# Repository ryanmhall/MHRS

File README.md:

# PPG-DaLiA heart-rate processing (single subject)

This README covers `ppg_analysis.py`. The script reads one subject from the PPG-DaLiA dataset and estimates heart rate from the wrist PPG. It then compares that estimate with the chest-ECG ground truth before and after a simple cleaning step.

**Requirements:** Python 3, `numpy`, `scipy`, `pandas`, `matplotlib`

**Run:** `ppg_analysis.py`. The file path is set at the top of the script.

## Pipeline at a glance

```
S1.pkl
 ├─ data['label'] ─────────────────────────────────────────► ground-truth HR (chest ECG)
 └─ data['signal']['wrist']['BVP']  (raw PPG, 64 Hz)
       │
       ├─ 1. band-pass 0.5–4 Hz (zero-phase Butterworth)
       ├─ 2. cut into 8 s windows, stepped every 2 s (same grid as the labels)
       ├─ 3. per window: Hann taper → zero-padded FFT → strongest peak in 40–200 BPM
       │                                                   ───► "Before" HR
       └─ 4. cleaning: band-edge rejection → running median → ±15 BPM gate
                       → running mean → gap interpolation   ───► "After" HR
```

## 1. Loading the data

- The `.pkl` file was written by Python 2, so it is opened with `pickle.load(f, encoding='latin1')`.
- **Raw PPG:** `data['signal']['wrist']['BVP']`. This is the blood volume pulse signal from the Empatica E4 wristband, sampled at **64 Hz** in arbitrary units. It is flattened to a 1-D array.
- **Ground truth:** `data['label']`. The dataset authors derived it from the chest ECG. Each value is the **average heart rate over an 8-second window**, and the windows advance **every 2 seconds**.
  - Label *i* covers seconds **[2i, 2i + 8)** of the recording.
  - That makes one label every 2 s, i.e. 0.5 Hz. This was the source of the original ~20 BPM offset: treating the labels as 2 Hz squeezed the ground-truth line into a quarter of the timeline.
  - Each label is plotted at the **centre of its window**, t = 2i + 4 s.

## 2. Band-pass filtering the raw PPG

- **Filter:** 2nd-order Butterworth band-pass, **0.5–4.0 Hz**, which corresponds to 30–240 BPM.
- **Applied with `filtfilt`:** the filter runs forward and then backward. This gives **zero phase shift**, so filtering doesn't move the signal in time, and the effective roll-off is 4th order.
- **Purpose:**
  - Remove slow baseline drift (DC level, respiration, sensor-contact changes) below 30 BPM.
  - Remove high-frequency noise above 240 BPM.
- Only the HR estimate uses the filtered signal. The bottom panel shows the **unfiltered** BVP.

## 3. Heart rate per window (the "Before" estimate)

Heart rate comes from the **dominant frequency** in each window, not from counting peaks.

1. **Windowing:** each estimate uses 8 s of filtered PPG, which is 512 samples. Window *i* spans samples 128·i to 128·i + 511, exactly matching label *i*, so there is one PPG estimate per ground-truth value.
2. **Hann taper:** the window is multiplied by a Hann function. Without it, the abrupt start and end of the segment would smear energy across frequencies (spectral leakage).
3. **Zero-padded FFT:** the 512 samples are padded to 8192 points before the FFT.
   - This puts spectrum points every 64 / 8192 Hz ≈ 0.0078 Hz ≈ **0.47 BPM**.
   - Zero-padding doesn't let the FFT separate two close frequencies; an 8 s window can only do that down to about 7.5 BPM. It does locate the single strongest peak far more precisely than unpadded bins would.
4. **Peak pick:** the magnitude spectrum is searched between **40 and 200 BPM**. The frequency of the largest value, × 60, is that window's heart rate.

This raw series appears in the **"Before"** panel. Its main error comes from wrist motion: arm swing, steps and hand movement add spectral peaks that are sometimes stronger than the pulse.

## 4. Cleaning (the "After" estimate)

The smoothing is a **median-gated moving average**. It is an outlier-rejection step (in the style of a Hampel filter) followed by a moving average of the values that survive.

**It uses only the PPG estimate. The ground truth is never used**, so the improvement shown in the "After" panel is legitimate.

| Step | What it does | Setting |
|---|---|---|
| a. Band-edge rejection | Marks estimates at the edge of the search band as missing. A "peak" at 40 or 200 BPM means the spectrum was still rising at the limit, from drift or motion, so it isn't a pulse. | ≤ 41 or ≥ 199 BPM |
| b. Running median | Takes the median of each estimate and its 7 neighbours on each side. This is a robust centre line that ignores isolated spikes. | 15 estimates = 30 s, centred |
| c. Outlier gate | Discards estimates further than the gate from that median. | ±15 BPM |
| d. Running mean | Averages the surviving estimates over the same span to smooth the step-like median. | 15 estimates = 30 s, centred |
| e. Gap fill | Where no estimates survived in a window, fills by linear interpolation between neighbours. | — |

**Notes:**
- Steps b and d use `min_periods=1`. Near the start and end of the recording, or around gaps, each value is computed from whatever estimates are available.
- **Centred vs. real time:** the centred window looks 14 s into the future. That is fine for offline analysis, but a wearable can't do it. Setting `center=False` in both `rolling()` calls gives a trailing (causal) filter. Use that when comparing against a real-time device; it delays the output by roughly 15 s.
- **Settings were chosen beforehand, not tuned on S1.** Tuning the span or gate to minimise error on this subject would fit the filter to the answer.

## 5. Metrics shown in the panel titles

Both metrics are computed over every window:

- **Bias** = mean(PPG HR − ECG HR). A negative bias means the PPG reads low on average.
- **MAE** = mean(|PPG HR − ECG HR|), in BPM.

## 6. Figure

1. **Before:** ECG ground truth (blue) and the raw per-window PPG estimate (orange).
2. **After:** ECG ground truth and the cleaned estimate (green). This panel uses the same y-axis range as the first so the two compare directly.
3. **Raw wrist PPG:** the unfiltered BVP. The y-axis view is limited to the 0.1–99.9th percentile plus a 10% margin so the largest motion spikes don't flatten the trace. **This affects the display only; the data is unchanged.**

The x-axes are linked, so zooming one panel zooms all three. The commented line `ax1.set_xlim(5, 8)` sets a fixed zoom.

## Limitations

- **Sustained motion artifact can't be fixed by smoothing.** When the raw estimate locks onto the motion frequency for minutes, as during parts of stair climbing and walking, the running median follows the wrong value. Fixing those stretches needs motion information, such as the wrist accelerometer, which this script doesn't use.
- **Smoothing flattens fast heart-rate changes.** A 30 s span cuts the peaks of short efforts like a stair climb.
- **Single subject:** results are for S1 only.

## Changes from the original script

| Original | Now | Why |
|---|---|---|
| `fs_hr = 2` (labels assumed 2 Hz) | Labels at 0.5 Hz, plotted at window centres | The 2 Hz assumption misaligned the ground truth in time and caused the ~20 BPM offset. |
| Peak count per 8 s window × 7.5 | Dominant FFT frequency per window | Counting peaks can only give values in 7.5 BPM steps. |
| `np.clip(hr, 40, 180)` | Band-edge values rejected, then cleaned | Clipping turned "no beats found" into fake 40 BPM readings. |
| No smoothing | Median-gated moving average | Removes isolated spikes without using the ground truth. |

## Companion script

`dalia_hr_overview.py` runs the same pipeline with extra diagnostics:

- timing checks
- error by activity
- tests for sampling-rate, alignment, harmonic and motion-lock errors
- activity shading on the plot
- command-line options

It uses a 4th-order band-pass and subtracts each window's mean before the FFT, so its numbers differ slightly from this script's.

## Data source

PPG-DaLiA, UCI Machine Learning Repository: https://archive.ics.uci.edu/dataset/495/ppg+dalia
Reiss, A., Indlekofer, I., Schmidt, P., Van Laerhoven, K. (2019). *Deep PPG: Large-scale heart rate estimation with convolutional neural networks.* Sensors 19(14), 3079. https://doi.org/10.3390/s19143079

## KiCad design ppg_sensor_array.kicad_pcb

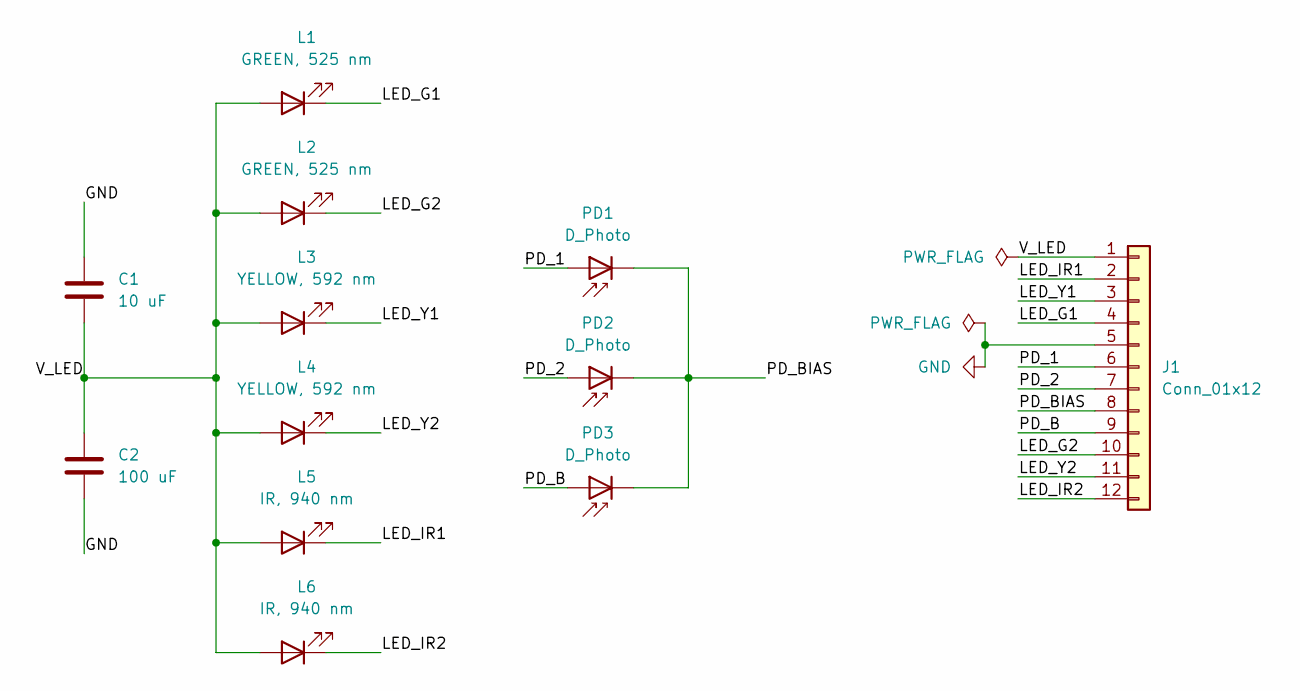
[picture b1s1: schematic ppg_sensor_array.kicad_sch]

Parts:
C1: 10 uF; C_0805_2012Metric_Pad1.18x1.45mm_HandSolder
C2: 100 uF; C_0805_2012Metric_Pad1.18x1.45mm_HandSolder
J1: Conn_01x12; PinHeader_1x12_P1.27mm_Vertical
L1, L2: GREEN, 525 nm; LED_0603_1608Metric_Pad1.05x0.95mm_HandSolder
L3, L4: YELLOW, 592 nm; LED_0603_1608Metric_Pad1.05x0.95mm_HandSolder
L5, L6: IR, 940 nm; LED_0603_1608Metric_Pad1.05x0.95mm_HandSolder
PD1, PD2, PD3: D_Photo; Osram_BPW34S-SMD

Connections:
/LED_G1: J1.4, L1.1 (K)
/LED_G2: J1.10, L2.1 (K)
/LED_IR1: J1.2, L5.1 (K)
/LED_IR2: J1.12, L6.1 (K)
/LED_Y1: J1.3, L3.1 (K)
/LED_Y2: J1.11, L4.1 (K)
/PD_1: J1.6, PD1.2 (A)
/PD_2: J1.7, PD2.2 (A)
/PD_B: J1.9, PD3.2 (A)
/PD_BIAS: J1.8, PD1.1 (K), PD2.1 (K), PD3.1 (K)
/V_LED: C1.2, C2.1, J1.1, L1.2 (A), L2.2 (A), L3.2 (A), L4.2 (A), L5.2 (A), L6.2 (A)
GND: C1.1, C2.2, J1.5

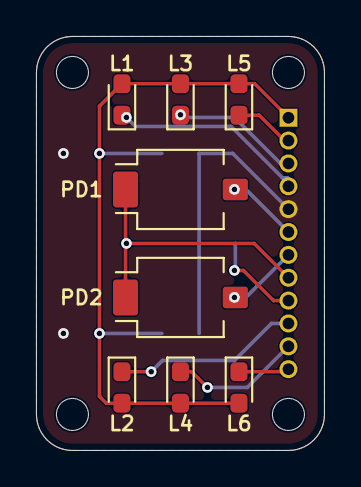
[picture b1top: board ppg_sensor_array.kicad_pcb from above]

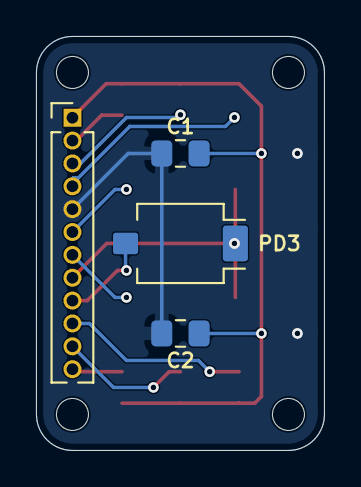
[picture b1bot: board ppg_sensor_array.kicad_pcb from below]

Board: 2 copper layers, 16.0 x 23.0 mm, 12 parts (4 on the bottom side), 12 nets.
